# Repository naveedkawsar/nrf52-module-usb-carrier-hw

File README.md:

# nrf52-module-usb-carrier-hw
USB-powered demo board for an E73-2G4M04S1B BLE module (based on the nRF52832) with some peripherals

<!--

-->

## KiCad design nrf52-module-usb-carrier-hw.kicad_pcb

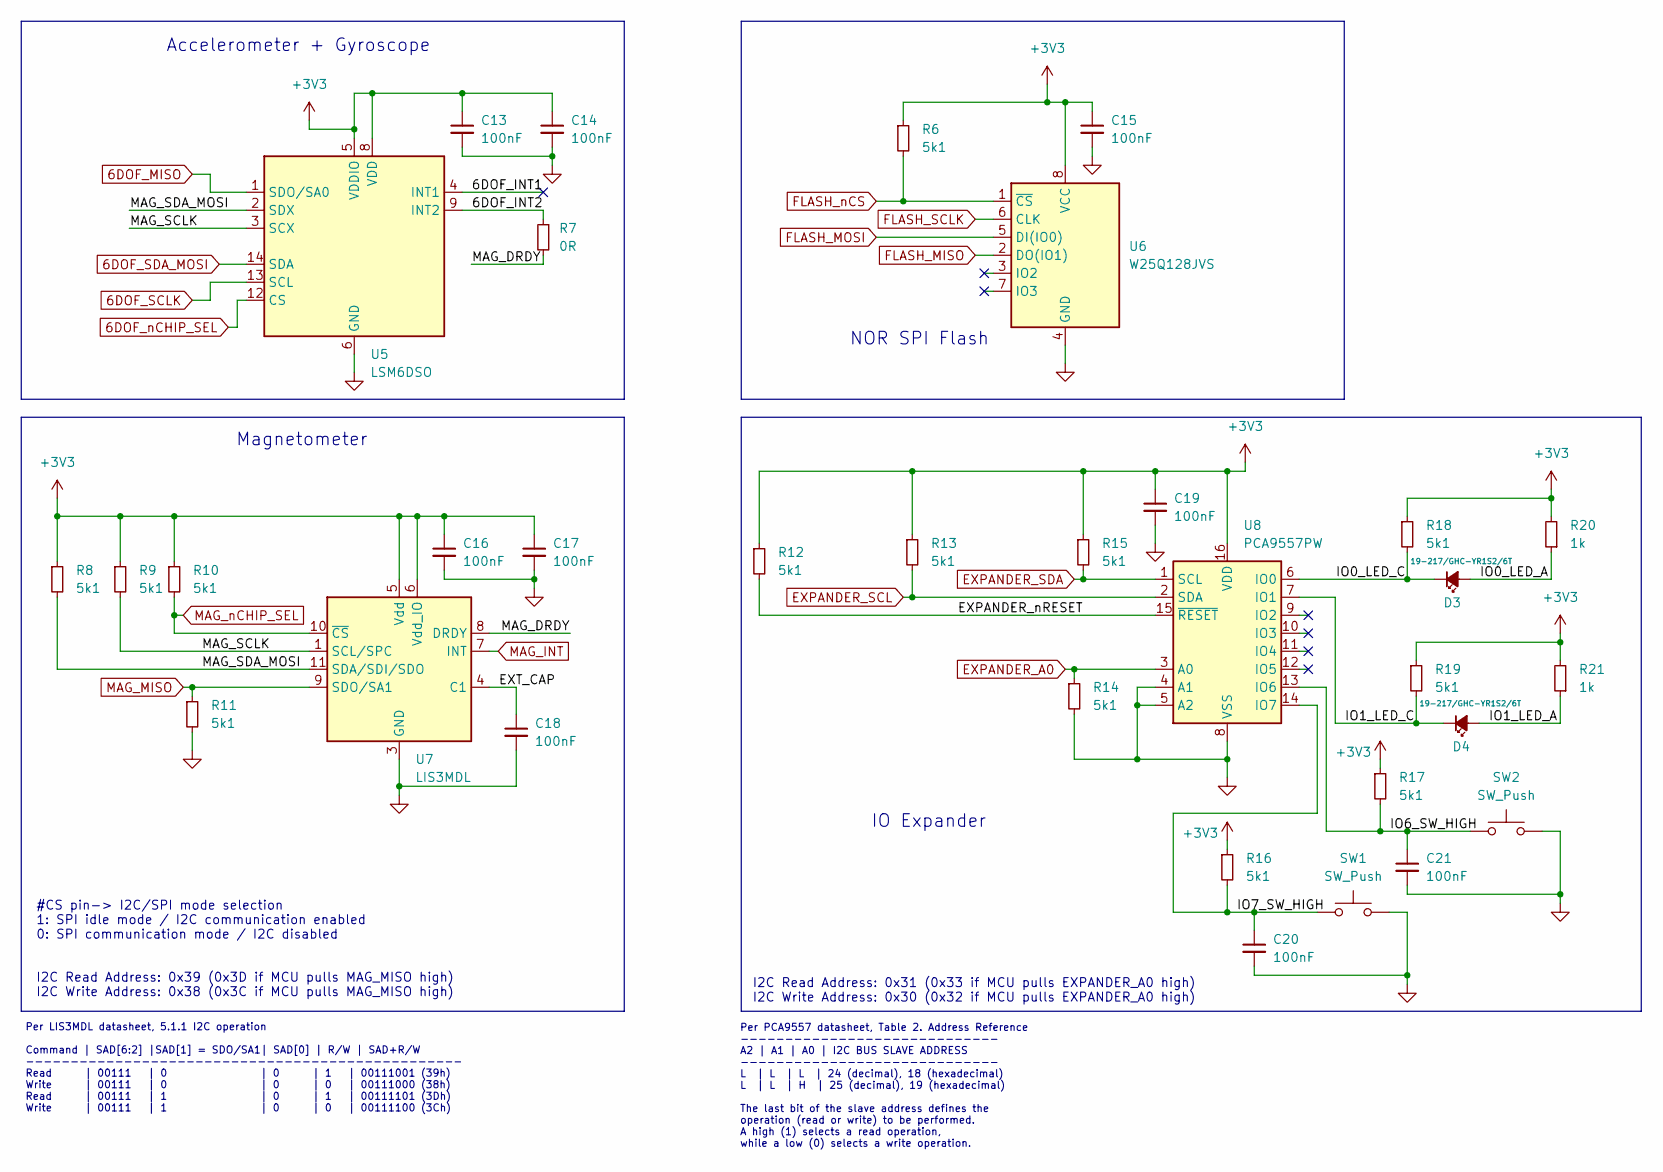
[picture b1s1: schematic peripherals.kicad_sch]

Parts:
C13, C14, C15, C16, C17, C18, C19, C20, C21: 100nF; C_0402_1005Metric; Manufacturer Part Number CL05B104KO5NNNC; LCSC Part # C1525
D3, D4: 19-217/GHC-YR1S2/6T; LED_0603_1608Metric; Manufacturer Part Number 19-217/GHC-YR1S2/6T; LCSC Part # C2986059
R6, R8, R9, R10, R11, R12, R13, R14, R15, R16, R17, R18, R19: 5k1; R_0603_1608Metric; Manufacturer Part Number 0603WAF5101T5E; LCSC Part # C23186
R7: 0R; R_0402_1005Metric; Manufacturer Part Number 0402WGF0000TCE; LCSC Part # C17168
R20, R21: 1k; R_0603_1608Metric; Manufacturer Part Number 0603WAF1001T5E; LCSC Part # C21190
SW1, SW2: SW_Push; SW_Push_1P1T_XKB_TS-1187A; LCSC Part # C318884
U5: LSM6DSO; LGA-14_3x2.5mm_P0.5mm_LayoutBorder3x4y; Manufacturer Part Number LSM6DSOTR; LCSC Part # C2829074
U6: W25Q128JVS; SOIC-8_5.23x5.23mm_P1.27mm; Manufacturer Part Number W25Q128JVSIQ; LCSC Part # C97521
U7: LIS3MDL; LGA-12_2x2mm_P0.5mm; Manufacturer Part Number LIS3MDLTR; LCSC Part # C478483
U8: PCA9557PW; TSSOP-16_4.4x5mm_P0.65mm; LCSC Part # C141380

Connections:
6DOF_MISO: U5.1 (SDO/SA0); also elsewhere on the board
6DOF_SCLK: U5.13 (SCL); also elsewhere on the board
6DOF_SDA_MOSI: U5.14 (SDA); also elsewhere on the board
6DOF_nCHIP_SEL: U5.12 (CS); also elsewhere on the board
+3V3: C13.1, C14.1, C15.1, C16.1, C17.1, C19.1, R6.1, R8.1, R9.1, R10.1, R12.1, R13.1, R15.1, R16.1, R17.1, R18.1, R19.1, R20.2, R21.2, U5.5 (VDDIO), U5.8 (VDD), U6.8 (VCC), U7.5 (Vdd), U7.6 (Vdd_IO), U8.16 (VDD); also elsewhere on the board
/Peripherals/6DOF_INT1: U5.4 (INT1)
/Peripherals/6DOF_INT2: R7.1, U5.9 (INT2)
/Peripherals/EXPANDER_nRESET: R12.2, U8.15 (~RESET)
/Peripherals/EXT_CAP: C18.1, U7.4 (C1)
/Peripherals/IO0_LED_A: D3.2 (A), R20.1
/Peripherals/IO0_LED_C: D3.1 (K), R18.2, U8.6 (IO0)
/Peripherals/IO1_LED_A: D4.2 (A), R21.1
/Peripherals/IO1_LED_C: D4.1 (K), R19.2, U8.7 (IO1)
/Peripherals/IO6_SW_HIGH: C21.1, R17.2, SW2.1, U8.13 (IO6)
/Peripherals/IO7_SW_HIGH: C20.1, R16.2, SW1.1, U8.14 (IO7)
/Peripherals/MAG_DRDY: R7.2, U7.8 (DRDY)
/Peripherals/MAG_SCLK: R9.2, U5.3 (SCX), U7.1 (SCL/SPC)
/Peripherals/MAG_SDA_MOSI: R8.2, U5.2 (SDX), U7.11 (SDA/SDI/SDO)
EXPANDER_A0: R14.1, U8.3 (A0); also elsewhere on the board
EXPANDER_SCL: R13.2, U8.2 (SDA); also elsewhere on the board
EXPANDER_SDA: R15.2, U8.1 (SCL); also elsewhere on the board
FLASH_MISO: U6.2 (DO(IO1)); also elsewhere on the board
FLASH_MOSI: U6.5 (DI(IO0)); also elsewhere on the board
FLASH_SCLK: U6.6 (CLK); also elsewhere on the board
FLASH_nCS: R6.2, U6.1 (~CS); also elsewhere on the board
GND: C13.2, C14.2, C15.2, C16.2, C17.2, C18.2, C19.2, C20.2, C21.2, R11.2, R14.2, SW1.2, SW2.2, U5.6 (GND), U5.7 (GND), U6.4 (GND), U7.2 (GND), U7.3 (GND), U7.12 (GND), U8.4 (A1), U8.5 (A2), U8.8 (VSS); also elsewhere on the board
MAG_INT: U7.7 (INT); also elsewhere on the board
MAG_MISO: R11.1, U7.9 (SDO/SA1); also elsewhere on the board
MAG_nCHIP_SEL: R10.2, U7.10 (~CS); also elsewhere on the board

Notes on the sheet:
Magnetometer
NOR SPI Flash
Accelerometer + Gyroscope
IO Expander
I2C Read Address: 0x39 (0x3D if MCU pulls MAG_MISO high) I2C Write Address: 0x38 (0x3C if MCU pulls MAG_MISO high)
Per LIS3MDL datasheet, 5.1.1 I2C operation Command | SAD[6:2] |SAD[1] = SDO/SA1| SAD[0] | R/W | SAD+R/W ------------------------------------------------- Read | 00111 | 0 | 0 | 1 | 00111001 (39h) Write | 00111 | 0 | 0 | 0 | 00111000 (38h) Read | 00111 | 1 | 0 | 1 | 00111101 (3Dh) Write | 00111 | 1 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
Per PCA9557 datasheet, Table 2. Address Reference ----------------------------- A2 | A1 | A0 | I2C BUS SLAVE ADDRESS ----------------------------- L | L | L | 24 (decimal), 18 (hexadecimal) L | L | H | 25 (decimal), 19 (hexadecimal) The last bit of the slave address defines the operation (read or w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
I2C Read Address: 0x31 (0x33 if MCU pulls EXPANDER_A0 high) I2C Write Address: 0x30 (0x32 if MCU pulls EXPANDER_A0 high)
#CS pin-> I2C/SPI mode selection 1: SPI idle mode / I2C communication enabled 0: SPI communication mode / I2C disabled

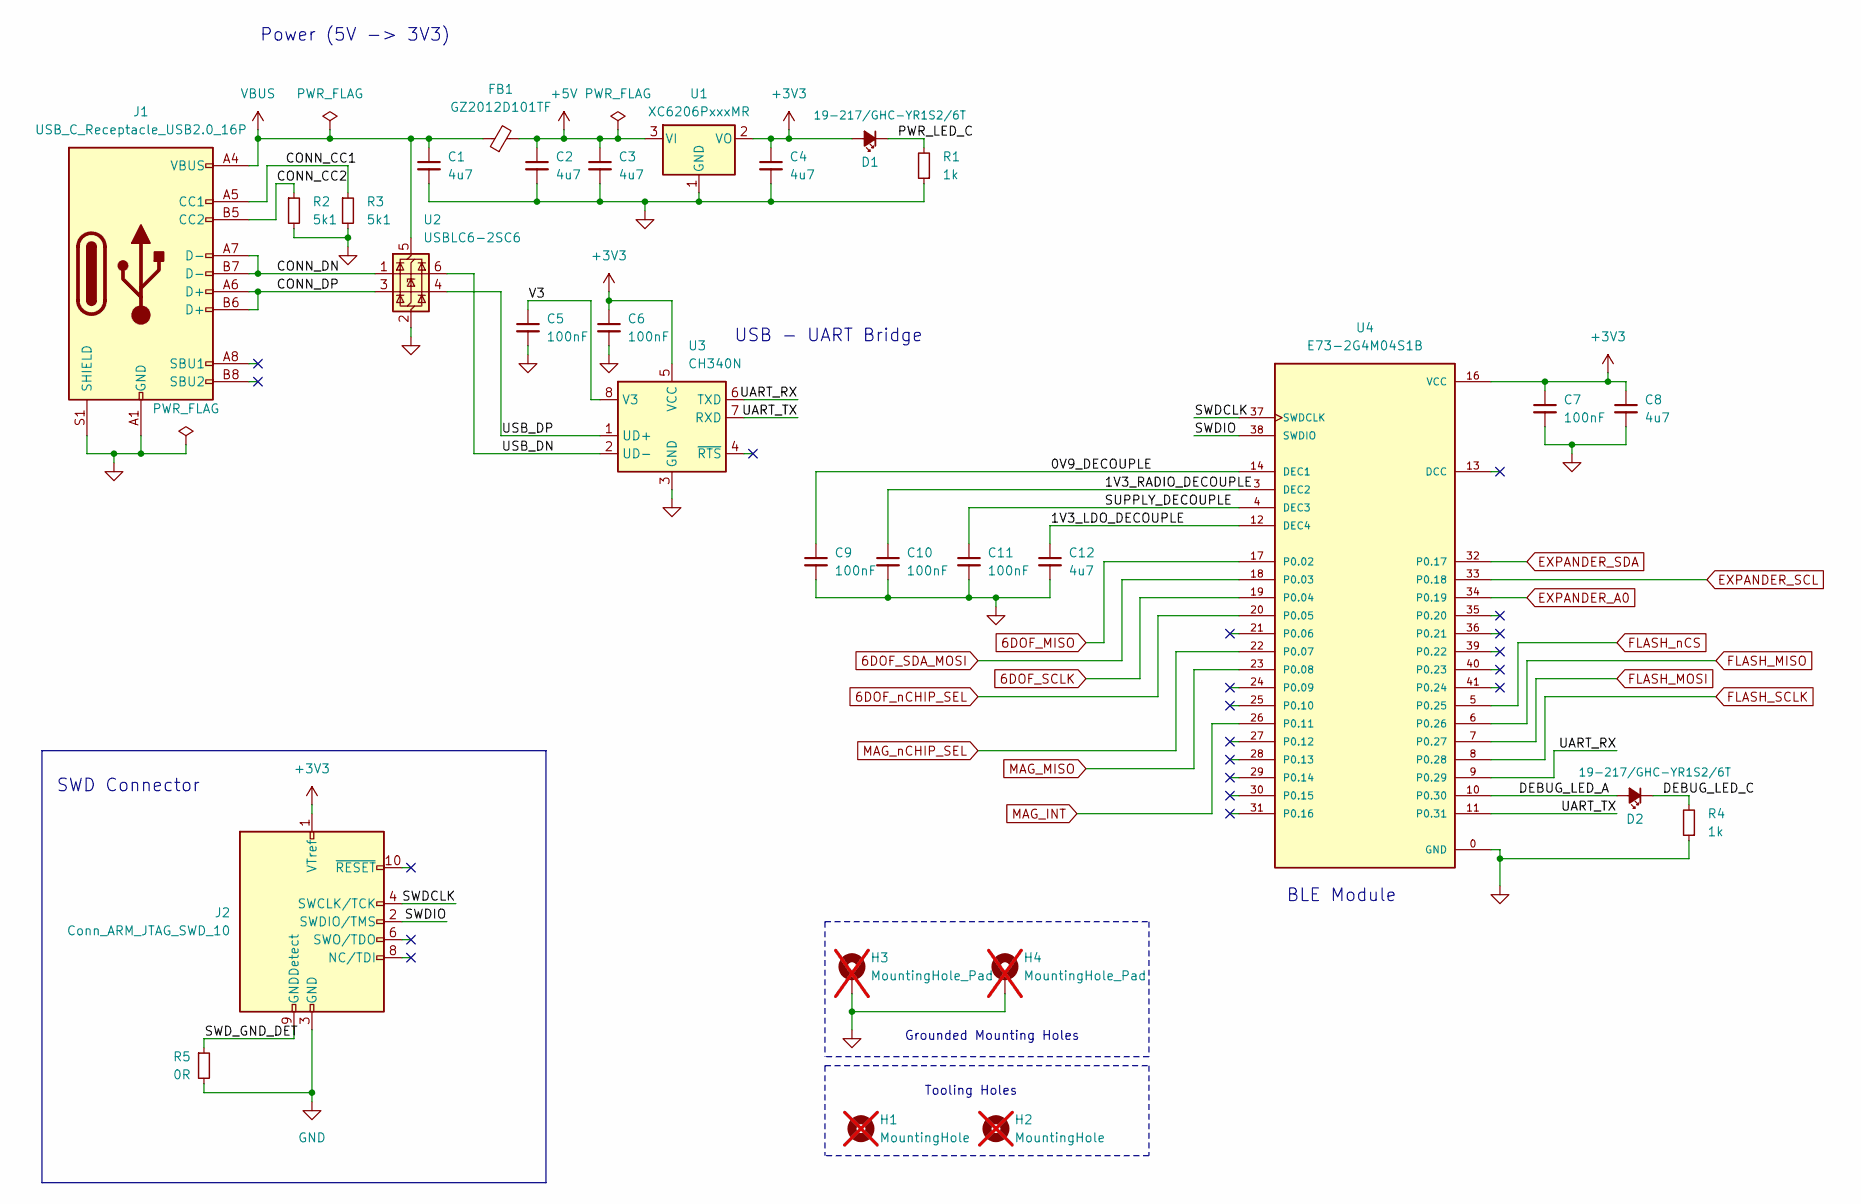
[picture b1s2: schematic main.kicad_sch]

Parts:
C1, C2, C3, C4, C8, C12: 4u7; C_0603_1608Metric; Manufacturer Part Number CL10A475KO8NNNC; LCSC Part # C19666
C5, C6, C7, C9, C10, C11: 100nF; C_0402_1005Metric; Manufacturer Part Number CL05B104KO5NNNC; LCSC Part # C1525
D1, D2: 19-217/GHC-YR1S2/6T; LED_0603_1608Metric; Manufacturer Part Number 19-217/GHC-YR1S2/6T; LCSC Part # C2986059
FB1: GZ2012D101TF; L_0805_2012Metric; Manufacturer Part Number GZ1608D101TF; LCSC Part # C1015
H1, H2: MountingHole; JLCPCB_ToolingHole_45.4mils; not fitted
H3, H4: MountingHole_Pad; MountingHole_2.2mm_M2_Pad; not fitted
J1: USB_C_Receptacle_USB2.0_16P; USB_C_Receptacle_XKB_U262-16XN-4BVC11; Manufacturer Part Number U262-161N-4BVC11; LCSC Part # C319148
J2: Conn_ARM_JTAG_SWD_10; PinHeader_2x05_P1.27mm_Vertical_SMD; Manufacturer Part Number 20021121-00010T4LF; LCSC Part # C598540
R1, R4: 1k; R_0603_1608Metric; Manufacturer Part Number 0603WAF1001T5E; LCSC Part # C21190
R2, R3: 5k1; R_0603_1608Metric; Manufacturer Part Number 0603WAF5101T5E; LCSC Part # C23186
R5: 0R; R_0402_1005Metric; Manufacturer Part Number 0402WGF0000TCE; LCSC Part # C17168
U1: XC6206PxxxMR; SOT-23-3; Manufacturer Part Number XC6206P332MR-G; LCSC Part # C5446
U2: USBLC6-2SC6; SOT-23-6; Manufacturer Part Number USBLC6-2SC6; LCSC Part # C2827654
U3: CH340N; SOP-8_3.9x4.9mm_P1.27mm; Manufacturer Part Number CH340N; LCSC Part # C2977777
U4: E73-2G4M04S1B; XCVR_E73-2G4M04S1B; PARTREV 1.4; LCSC Part # C411306

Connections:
6DOF_MISO: U4.17 (P0.02); also elsewhere on the board
6DOF_SCLK: U4.19 (P0.04); also elsewhere on the board
6DOF_SDA_MOSI: U4.18 (P0.03); also elsewhere on the board
6DOF_nCHIP_SEL: U4.20 (P0.05); also elsewhere on the board
+3V3: C4.1, C6.1, C7.1, C8.1, D1.2 (A), J2.1 (VTref), U1.2 (VO), U3.5 (VCC), U4.16 (VCC); also elsewhere on the board
+5V: C2.1, C3.1, FB1.2, U1.3 (VI)
/Power + MCU + SWD/0V9_DECOUPLE: C9.1, U4.14 (DEC1)
/Power + MCU + SWD/1V3_LDO_DECOUPLE: C12.1, U4.12 (DEC4)
/Power + MCU + SWD/1V3_RADIO_DECOUPLE: C10.1, U4.3 (DEC2)
/Power + MCU + SWD/CONN_CC1: J1.A5 (CC1), R3.1
/Power + MCU + SWD/CONN_CC2: J1.B5 (CC2), R2.1
/Power + MCU + SWD/CONN_DN: J1.A7 (D-), J1.B7 (D-), U2.1 (I/O1)
/Power + MCU + SWD/CONN_DP: J1.A6 (D+), J1.B6 (D+), U2.3 (I/O2)
/Power + MCU + SWD/DEBUG_LED_A: D2.2 (A), U4.10 (P0.30)
/Power + MCU + SWD/DEBUG_LED_C: D2.1 (K), R4.2
/Power + MCU + SWD/PWR_LED_C: D1.1 (K), R1.2
/Power + MCU + SWD/SUPPLY_DECOUPLE: C11.1, U4.4 (DEC3)
/Power + MCU + SWD/SWDCLK: J2.4 (SWCLK/TCK), U4.37 (SWDCLK)
/Power + MCU + SWD/SWDIO: J2.2 (SWDIO/TMS), U4.38 (SWDIO)
/Power + MCU + SWD/SWD_GND_DET: J2.9 (GNDDetect), R5.1
/Power + MCU + SWD/UART_RX: U3.6 (TXD), U4.9 (P0.29)
/Power + MCU + SWD/UART_TX: U3.7 (RXD), U4.11 (P0.31)
/Power + MCU + SWD/USB_DN: U2.6 (I/O1), U3.2 (UD-)
/Power + MCU + SWD/USB_DP: U2.4 (I/O2), U3.1 (UD+)
/Power + MCU + SWD/V3: C5.1, U3.8 (V3)
EXPANDER_A0: U4.34 (P0.19); also elsewhere on the board
EXPANDER_SCL: U4.33 (P0.18); also elsewhere on the board
EXPANDER_SDA: U4.32 (P0.17); also elsewhere on the board
FLASH_MISO: U4.6 (P0.26); also elsewhere on the board
FLASH_MOSI: U4.7 (P0.27); also elsewhere on the board
FLASH_SCLK: U4.8 (P0.28); also elsewhere on the board
FLASH_nCS: U4.5 (P0.25); also elsewhere on the board
GND: C1.2, C2.2, C3.2, C4.2, C5.2, C6.2, C7.2, C8.2, C9.2, C10.2, C11.2, C12.2, H3.1, H4.1, J1.A1 (GND), J1.A12 (GND), J1.B1 (GND), J1.B12 (GND), J1.S1 (SHIELD), J2.3 (GND), J2.5 (GND), R1.1, R2.2, R3.2, R4.1, R5.2, U1.1 (GND), U2.2 (GND), U3.3 (GND), U4.0 (GND), U4.1 (GND), U4.2 (GND), U4.15 (GND), U4.42 (GND), U4.43 (GND); also elsewhere on the board
MAG_INT: U4.26 (P0.11); also elsewhere on the board
MAG_MISO: U4.23 (P0.08); also elsewhere on the board
MAG_nCHIP_SEL: U4.22 (P0.07); also elsewhere on the board
VBUS: C1.1, FB1.1, J1.A4 (VBUS), J1.A9 (VBUS), J1.B4 (VBUS), J1.B9 (VBUS), U2.5 (VBUS)

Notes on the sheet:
USB - UART Bridge
Grounded Mounting Holes
Tooling Holes
Power (5V -> 3V3)
BLE Module
SWD Connector

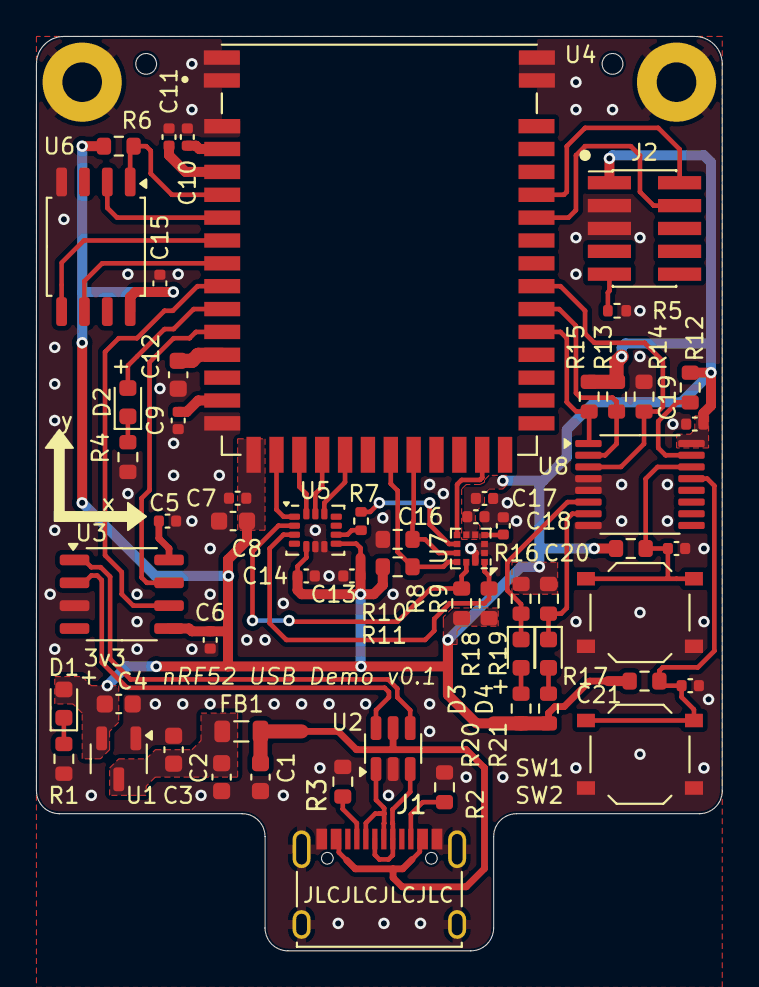
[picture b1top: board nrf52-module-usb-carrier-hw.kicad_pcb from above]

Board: 2 copper layers, 38.1 x 50.8 mm, 63 parts (0 on the bottom side), 49 nets.

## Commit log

2024-05-14 Initial commit of schematic with nRF module, SPI Flash, IMU sensors. Plus PCB file with WIP placement of module and USB connectors
2024-05-16 Routed diff pairs, IMU sensors, SPI Flash
2024-05-19 Added an I2C IO expander, plus 2 pushbuttons and 2 LEDs controlled by the expander
2024-05-19 PWR and GND netclass cleanup
2024-05-19 Started routing power
2024-05-19 Updated PCB file to handle DRC. No errors, few warnings remaining
2024-05-19 Cleaned up schematic with comments from datasheets. Added stitching vias to PCB
2024-05-19 Switched around debug LED pinout with a UART line to be compatible with a previous design
2024-05-20 Brought out INT pin from magnetometer to MCU, in case of need. Updated layout accordingly
2024-05-20 Exported BOM, pick-and-place files. Finalized schematic and exported PDF. Files used to place JLCPCB order
2024-06-19 Added ReadMe with KiCAD render screenshots
2024-06-19 Update README.md
    Corrected paths to screenshots
2024-06-19 Update README.md
    Resized images in ReadMe
